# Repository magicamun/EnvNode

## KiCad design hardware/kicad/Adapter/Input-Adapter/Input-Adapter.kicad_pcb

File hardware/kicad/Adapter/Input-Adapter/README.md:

# Input Adapter — revision 0.1

Passive-DUT measurement adapter for the [Test Controller](../../MainBoards/Test-Controller/README.md).
Three CD74HC4067 multiplexers select one of **40 independent measurement inputs**:
38 ESP32 socket contacts plus MB_3V3_SYS and MB_GND. The adapter contains no ESP32.

## Connectors and power

- **J4:** DUT test plug, 2 × 19 pins, 2.54 mm pitch, 25.40 mm row spacing. From the
  top, left pins run 1–19 and right pins run 38–20. Remove the DUT ESP32 before use.
- **TP1:** two-pin header for the reference pigtail: pin 1 MB_GND, pin 2 MB_3V3_SYS.
  The cable terminates in the agreed two-pin JST-PH on a suitably revised mainboard.
  Both are measurement contacts, not adapter supply connections.
- **J1:** 2 × 5 IDC header, 2.54 mm pitch. Connect pin-for-pin to Controller J8.
  Use matching pin-1 markings and keyed cable assembly; do not assume orientation
  from connector placement on the PCB.
- J1 supplies 3V3_SYS and GND. C1–C3 provide 100 nF local decoupling for U4–U6.
  MB_GND and all DUT socket contacts remain separate from adapter supply GND.
- COM is shared by U4–U6. Enable only one multiplexer at a time. Active-low enable
  pull-ups and the ADC pulldown/filter are on the Controller, not this adapter.

## J1 cable contract

| Pin | Signal | Controller GPIO / function |
| ---: | --- | --- |
| 1 | 3V3_SYS | Adapter supply |
| 2 | GND | Supply ground |
| 3 | IN_EN1 | GPIO14; U4 enable, active low |
| 4 | IN_S3 | GPIO13 |
| 5 | IN_EN2 | GPIO26; U5 enable, active low |
| 6 | IN_S2 | GPIO27 |
| 7 | IN_EN3 | GPIO33; U6 enable, active low |
| 8 | IN_S1 | GPIO25 |
| 9 | COM / COM_IN | GPIO34 / ADC1 |
| 10 | IN_S0 | GPIO32 |

## Input routing contract

Logical inputs 1–38 retain the DUT socket numbering. Logical inputs 39 and
40 are the added reference contacts; these are not additional ESP32 socket pins.
I0–I15 denote analog multiplexer channels; S0 is the least-significant address bit.
The table records the saved PCB wiring, not a presumed sequential layout.

| Logical input | Connector.pad | Net | Multiplexer | Channel | IC pad |
| ---: | --- | --- | --- | --- | ---: |
| 1 | J4.1 | L01 | U4 | I7 | 2 |
| 2 | J4.2 | L02 | U4 | I6 | 3 |
| 3 | J4.3 | L03 | U4 | I5 | 4 |
| 4 | J4.4 | L04 | U4 | I4 | 5 |
| 5 | J4.5 | L05 | U4 | I3 | 6 |
| 6 | J4.6 | L06 | U4 | I2 | 7 |
| 7 | J4.7 | L07 | U4 | I1 | 8 |
| 8 | J4.8 | L08 | U4 | I0 | 9 |
| 9 | J4.9 | L09 | U5 | I7 | 2 |
| 10 | J4.10 | L10 | U5 | I6 | 3 |
| 11 | J4.11 | L11 | U5 | I5 | 4 |
| 12 | J4.12 | L12 | U5 | I4 | 5 |
| 13 | J4.13 | L13 | U5 | I3 | 6 |
| 14 | J4.14 | L14 | U5 | I2 | 7 |
| 15 | J4.15 | L15 | U6 | I7 | 2 |
| 16 | J4.16 | L16 | U6 | I6 | 3 |
| 17 | J4.17 | L17 | U6 | I5 | 4 |
| 18 | J4.18 | L18 | U6 | I4 | 5 |
| 19 | J4.19 | L19 | U6 | I3 | 6 |
| 20 | J4.20 | R19 | U6 | I12 | 19 |
| 21 | J4.21 | R18 | U6 | I11 | 20 |
| 22 | J4.22 | R17 | U6 | I10 | 21 |
| 23 | J4.23 | R16 | U6 | I9 | 22 |
| 24 | J4.24 | R15 | U6 | I8 | 23 |
| 25 | J4.25 | R14 | U5 | I13 | 18 |
| 26 | J4.26 | R13 | U5 | I12 | 19 |
| 27 | J4.27 | R12 | U5 | I11 | 20 |
| 28 | J4.28 | R11 | U5 | I10 | 21 |
| 29 | J4.29 | R10 | U5 | I9 | 22 |
| 30 | J4.30 | R09 | U5 | I8 | 23 |
| 31 | J4.31 | R08 | U4 | I15 | 16 |
| 32 | J4.32 | R07 | U4 | I14 | 17 |
| 33 | J4.33 | R06 | U4 | I13 | 18 |
| 34 | J4.34 | R05 | U4 | I12 | 19 |
| 35 | J4.35 | R04 | U4 | I11 | 20 |
| 36 | J4.36 | R03 | U4 | I10 | 21 |
| 37 | J4.37 | R02 | U4 | I9 | 22 |
| 38 | J4.38 | R01 | U4 | I8 | 23 |
| 39 | TP1.2 | MB_3V3_SYS | U6 | I13 | 18 |
| 40 | TP1.1 | MB_GND | U6 | I14 | 17 |

## Operation and firmware status

Continuity testing requires an unpowered DUT, its ESP32 removed, and the separate
provisioning cable disconnected. Connect the reference pigtail only to a compatible
DUT revision. Mainboard-side series protection diodes make the reference paths
unidirectional; thresholds and test current direction require physical validation.

Test firmware 0.4.0 supports 38- or 40-input profiles in its model, simulation,
comparisons and UI. The revision-0.1 fixture mapping is generated from the three
PCBs by `firmware/scripts/generate_fixture_routing.py`. Bundled legacy profiles
still use 38 inputs; new reference-aware mainboard profiles remain to be added.
The new references must not be silently treated as present on old mainboards.
Physical I/O, switching sequence and ADC settling/thresholds remain unvalidated.

The monolithic Test-Provisioning project is superseded by Input-Adapter,
Test-Controller and Module-Adapter. Earlier revisions remain in Git history.

EnvNode-owned files follow the repository LICENSE (LicenseRef-EnvNode-Use-and-Redistribution-1.0).

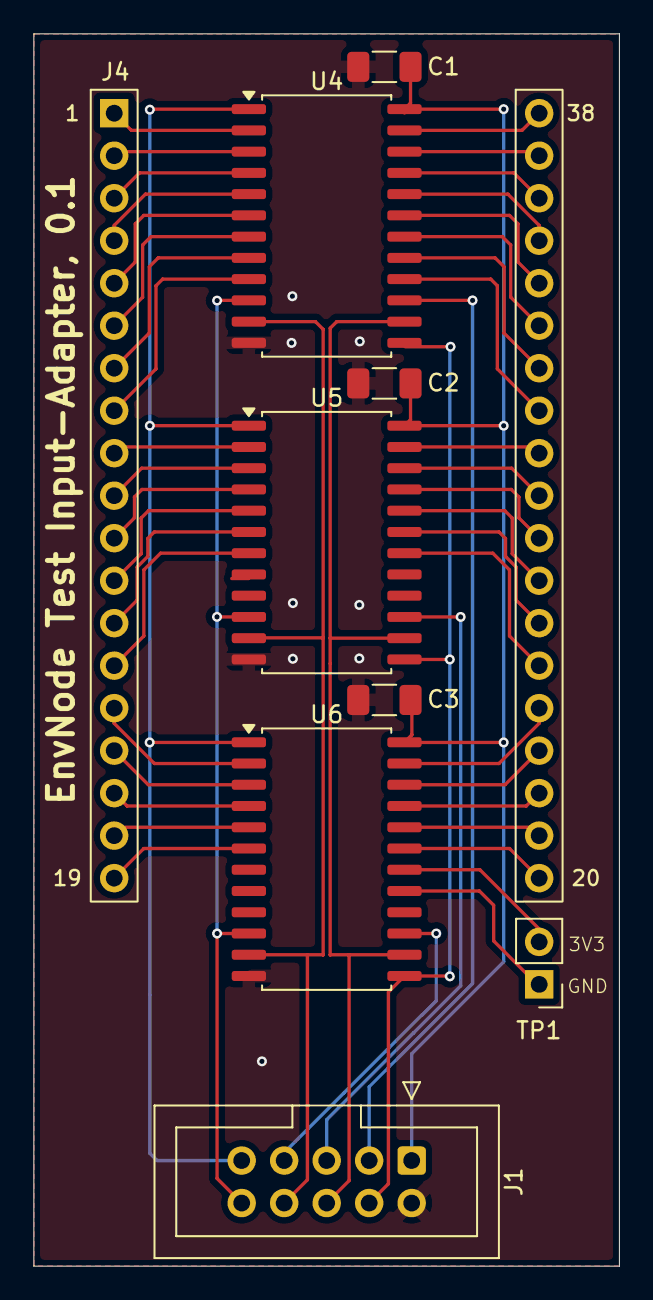
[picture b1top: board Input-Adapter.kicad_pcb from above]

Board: 2 copper layers, 35.0 x 73.7 mm, 9 parts (0 on the bottom side), 50 nets.

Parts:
C1, C2, C3: 100nF; C_1206_3216Metric_Pad1.33x1.80mm_HandSolder
J1: Conn_02x05_Odd_Even; IDC-Header_2x05_P2.54mm_Vertical
J4: ESP32_DevKitC_TestPlug; ESP32_DevKitC_TestPlug_2x19_P2.54mm_Row25.40mm
TP1: Conn_01x02_Socket; PinHeader_1x02_P2.54mm_Vertical
U4, U5, U6: CD74HC4067M; SOIC-24W_7.5x15.4mm_P1.27mm

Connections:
3V3_SYS: C1.2, C2.2, C3.2, J1.1, U4.24 (VCC), U5.24 (VCC), U6.24 (VCC)
/COM: J1.9, U4.1 (COM), U5.1 (COM), U6.1 (COM)
/IN/L01: J4.1 (L01), U4.2 (I7)
/IN/L02: J4.2 (L02), U4.3 (I6)
/IN/L03: J4.3 (L03), U4.4 (I5)
/IN/L04: J4.4 (L04), U4.5 (I4)
/IN/L05: J4.5 (L05), U4.6 (I3)
/IN/L06: J4.6 (L06), U4.7 (I2)
/IN/L07: J4.7 (L07), U4.8 (I1)
/IN/L08: J4.8 (L08), U4.9 (I0)
/IN/L09: J4.9 (L09), U5.2 (I7)
/IN/L10: J4.10 (L10), U5.3 (I6)
/IN/L11: J4.11 (L11), U5.4 (I5)
/IN/L12: J4.12 (L12), U5.5 (I4)
/IN/L13: J4.13 (L13), U5.6 (I3)
/IN/L14: J4.14 (L14), U5.7 (I2)
/IN/L15: J4.15 (L15), U6.2 (I7)
/IN/L16: J4.16 (L16), U6.3 (I6)
/IN/L17: J4.17 (L17), U6.4 (I5)
/IN/L18: J4.18 (L18), U6.5 (I4)
/IN/L19: J4.19 (L19), U6.6 (I3)
/IN/MB_3V3_SYS: TP1.2, U6.18 (I13)
/IN/MB_GND: TP1.1, U6.17 (I14)
/IN/R01: J4.38 (R01), U4.23 (I8)
/IN/R02: J4.37 (R02), U4.22 (I9)
/IN/R03: J4.36 (R03), U4.21 (I10)
/IN/R04: J4.35 (R04), U4.20 (I11)
/IN/R05: J4.34 (R05), U4.19 (I12)
/IN/R06: J4.33 (R06), U4.18 (I13)
/IN/R07: J4.32 (R07), U4.17 (I14)
/IN/R08: J4.31 (R08), U4.16 (I15)
/IN/R09: J4.30 (R09), U5.23 (I8)
/IN/R10: J4.29 (R10), U5.22 (I9)
/IN/R11: J4.28 (R11), U5.21 (I10)
/IN/R12: J4.27 (R12), U5.20 (I11)
/IN/R13: J4.26 (R13), U5.19 (I12)
/IN/R14: J4.25 (R14), U5.18 (I13)
/IN/R15: J4.24 (R15), U6.23 (I8)
/IN/R16: J4.23 (R16), U6.22 (I9)
/IN/R17: J4.22 (R17), U6.21 (I10)
/IN/R18: J4.21 (R18), U6.20 (I11)
/IN/R19: J4.20 (R19), U6.19 (I12)
/IN_EN1: J1.3, U4.15 (~E)
/IN_EN2: J1.5, U5.15 (~E)
/IN_EN3: J1.7, U6.15 (~E)
/IN_S0: J1.10, U4.10 (S0), U5.10 (S0), U6.10 (S0)
/IN_S1: J1.8, U4.11 (S1), U5.11 (S1), U6.11 (S1)
/IN_S2: J1.6, U4.14 (S2), U5.14 (S2), U6.14 (S2)
/IN_S3: J1.4, U4.13 (S3), U5.13 (S3), U6.13 (S3)
GND: C1.1, C2.1, C3.1, J1.2, U4.12 (GND), U5.12 (GND), U6.12 (GND)

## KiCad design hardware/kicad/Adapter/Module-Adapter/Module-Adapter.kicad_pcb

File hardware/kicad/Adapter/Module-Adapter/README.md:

# Module Adapter — revision 0.2

Passive test adapter between the [Test Controller](../../MainBoards/Test-Controller/README.md)
module-test output and a DUT module slot. This is not a functional module template:
there is no identification EEPROM, sensor, actuator or local power source.

- **J4:** top-side 2 × 7 IDC header, 2.54 mm pitch, connected pin-for-pin to
  Controller J3 using the matching keyed ribbon cable.
- **J1:** bottom-mounted 2 × 7 THT pin header for the DUT module socket, using
  `EnvNode-Footprints:PinHeader_2x07_P2.54mm_Vertical_Bottom`.
- **H1:** 2.7 mm mounting hole for mechanical support.
- All 14 channels connect **J4.n → J1.n** without remapping. The copper plane
  belongs only to module test contact 1 (GND); it is not an independent supply return.

## Pin contract

| Pin | DUT interface signal |
| ---: | --- |
| 1 | GND |
| 2 | +3V3_SYS |
| 3 | EEPROM_A0 (slot-dependent address strap) |
| 4 | +5V |
| 5 | I2C0_SDA |
| 6 | I2C0_SCL |
| 7 | I2C1_SDA |
| 8 | I2C1_SCL |
| 9 | AUX_GPIO1 |
| 10 | AUX_GPIO2 |
| 11 | SPI_MOSI |
| 12 | SPI_MISO |
| 13 | SPI_SCK |
| 14 | SPI_CS |

These are test contact names, not rails driven continuously by the adapter.
The selected DUT profile determines slot-specific GPIOs and whether EEPROM_A0
is tied to GND or 3V3_SYS. All contacts must remain separately selectable at the
Controller output multiplexer. Check pin-1 orientation at both ribbon connectors
and at the bottom-mounted DUT plug; use the saved pad numbering rather than
inferring numbering from a top-view image.

Continuity testing requires an unpowered DUT, removed DUT ESP32 and disconnected
provisioning cable. Move the one module adapter between slots only between tests.
See the [module-interface specification](../../../../docs/EnvNode_Module_Interface_Hardware_Specification.md).

The project footprint library path is relative to this directory:
`${KIPRJMOD}/../../Libraries/EnvNode-Footprints.pretty`. Rerun ERC/DRC after any
connector, library or routing change. Physical fit and electrical behavior still
require validation on the assembled hardware.

EnvNode-owned files follow the repository LICENSE (LicenseRef-EnvNode-Use-and-Redistribution-1.0).

Revision 0.2 rotates the IDC header for cable routing. All 14 contacts remain
pin-for-pin; use a straight IDC cable and verify pin-1 orientation. CAD reviewed;
physical acceptance of the new revision remains pending.

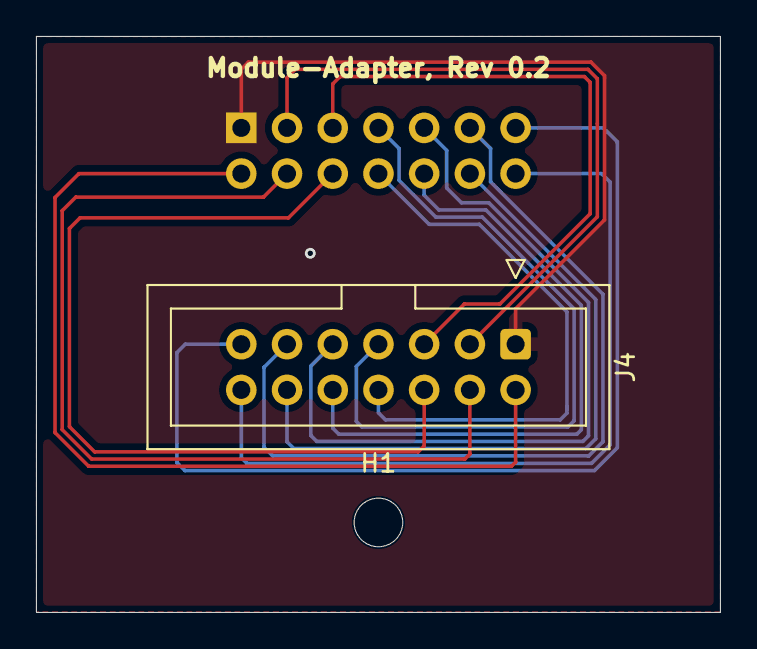
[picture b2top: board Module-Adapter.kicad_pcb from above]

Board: 2 copper layers, 38.0 x 32.0 mm, 3 parts (1 on the bottom side), 14 nets.

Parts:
H1: MountingHole; MountingHole_2.7mm_M2.5_DIN965
J1: Conn_02x07_Odd_Even; PinHeader_2x07_P2.54mm_Vertical_Bottom
J4: Conn_02x07_Odd_Even; IDC-Header_2x07_P2.54mm_Vertical

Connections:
/+3V3_SYS: J1.2, J4.2
/+5V: J1.4, J4.4
/AUX_GPIO1: J1.9, J4.9
/AUX_GPIO2: J1.10, J4.10
/EEPROM_A0: J1.3, J4.3
/GND: J1.1, J4.1
/I2C0_SCL: J1.6, J4.6
/I2C0_SDA: J1.5, J4.5
/I2C1_SCL: J1.8, J4.8
/I2C1_SDA: J1.7, J4.7
/SPI_CS: J1.14, J4.14
/SPI_MISO: J1.12, J4.12
/SPI_MOSI: J1.11, J4.11
/SPI_SCK: J1.13, J4.13

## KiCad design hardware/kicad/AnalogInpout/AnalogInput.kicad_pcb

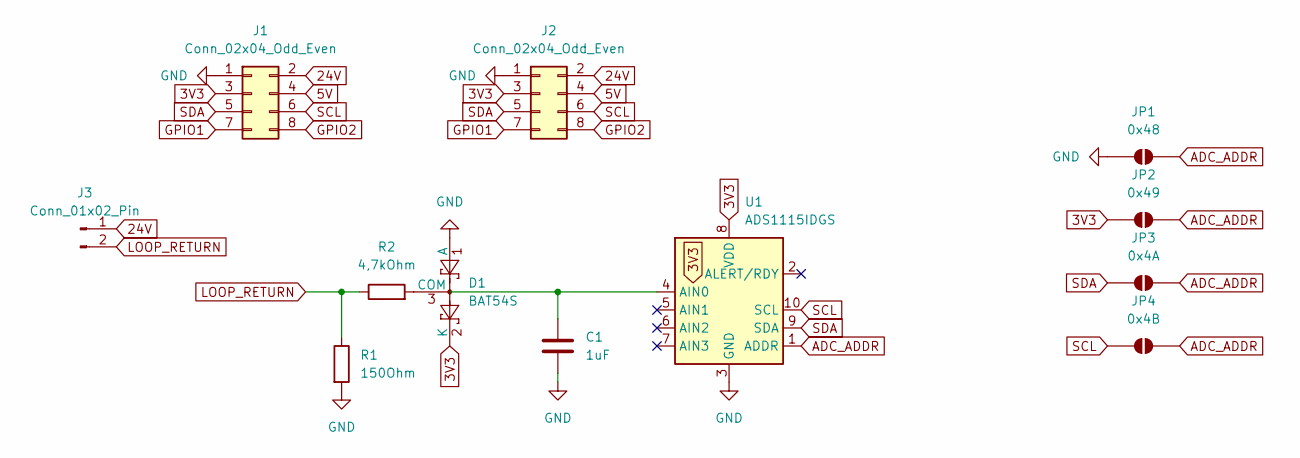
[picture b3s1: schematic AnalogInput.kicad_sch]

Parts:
C1: 1uF; C_1206_3216Metric_Pad1.33x1.80mm_HandSolder
D1: BAT54S; SOT-23
J1, J2: Conn_02x04_Odd_Even; PinSocket_2x04_P2.54mm_Vertical_Bottom
J3: Conn_01x02_Pin; PinSocket_1x02_P2.54mm_Vertical
JP1: 0x48; SolderJumper-2_P1.3mm_Open_Pad1.0x1.5mm
JP2: 0x49; SolderJumper-2_P1.3mm_Open_Pad1.0x1.5mm
JP3: 0x4A; SolderJumper-2_P1.3mm_Open_Pad1.0x1.5mm
JP4: 0x4B; SolderJumper-2_P1.3mm_Open_Pad1.0x1.5mm
R1: 150Ohm; R_1206_3216Metric_Pad1.30x1.75mm_HandSolder
R2: 4,7kOhm; R_1206_3216Metric_Pad1.30x1.75mm_HandSolder
U1: ADS1115IDGS; TSSOP-10_3x3mm_P0.5mm

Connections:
3V3: D1.2 (K), J1.3, J2.3, JP2.1 (A), U1.8 (VDD)
5V: J1.4, J2.4
24V: J1.2, J2.2, J3.1
ADC_ADDR: JP1.2 (B), JP2.2 (B), JP3.2 (B), JP4.2 (B), U1.1 (ADDR)
GND: C1.2, D1.1 (A), J1.1, J2.1, JP1.1 (A), R1.2, U1.3 (GND)
GPIO1: J1.7, J2.7
GPIO2: J1.8, J2.8
LOOP_RETURN: J3.2, R1.1, R2.1
unnamed: D1.3 (COM), R2.2
unnamed: C1.1, U1.4 (AIN0)
SCL: J1.6, J2.6, JP4.1 (A), U1.10 (SCL)
SDA: J1.5, J2.5, JP3.1 (A), U1.9 (SDA)

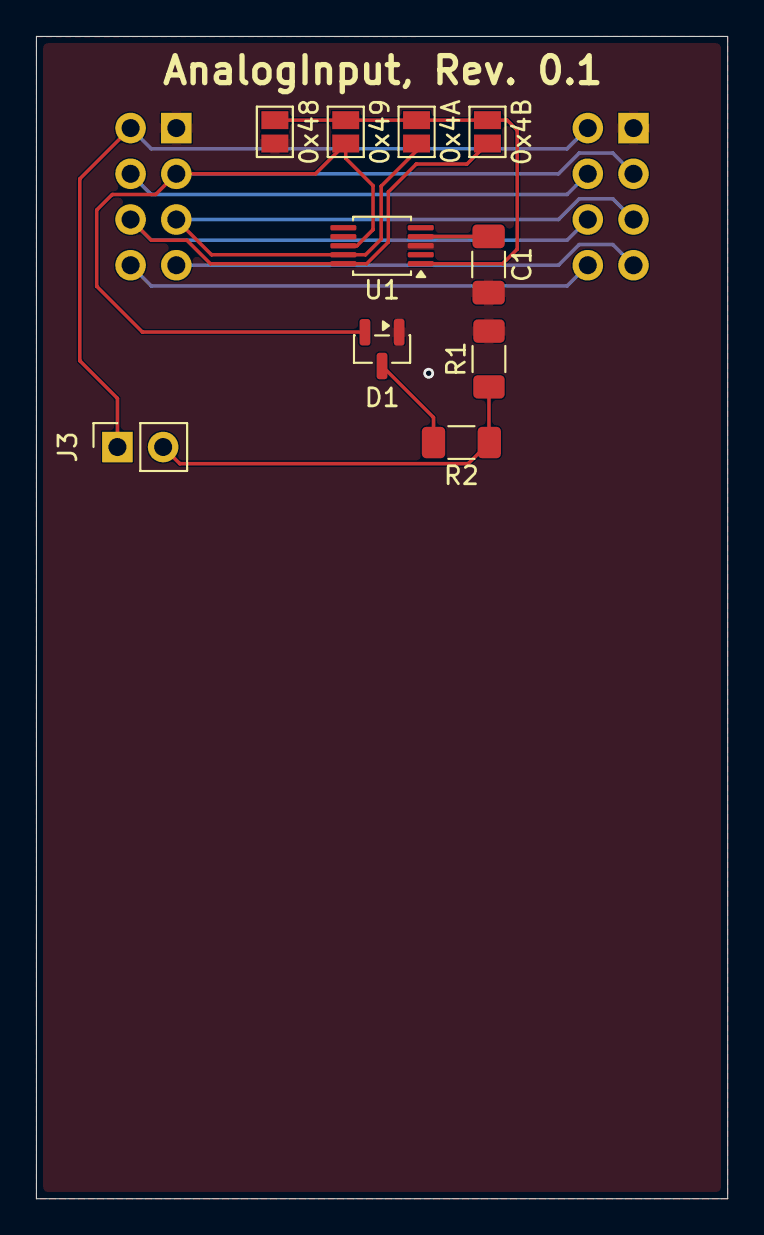
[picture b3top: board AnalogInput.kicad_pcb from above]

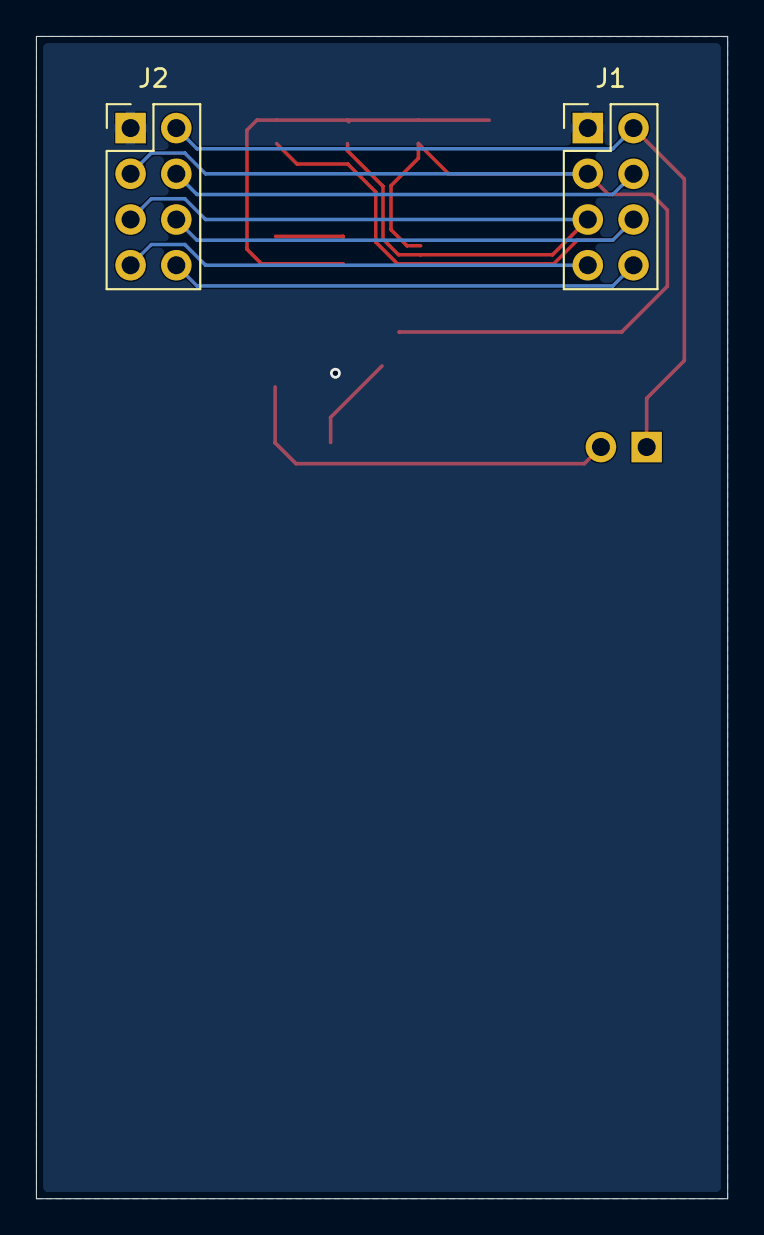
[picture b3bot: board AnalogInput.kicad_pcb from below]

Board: 2 copper layers, 38.4 x 64.6 mm, 12 parts (2 on the bottom side), 12 nets.

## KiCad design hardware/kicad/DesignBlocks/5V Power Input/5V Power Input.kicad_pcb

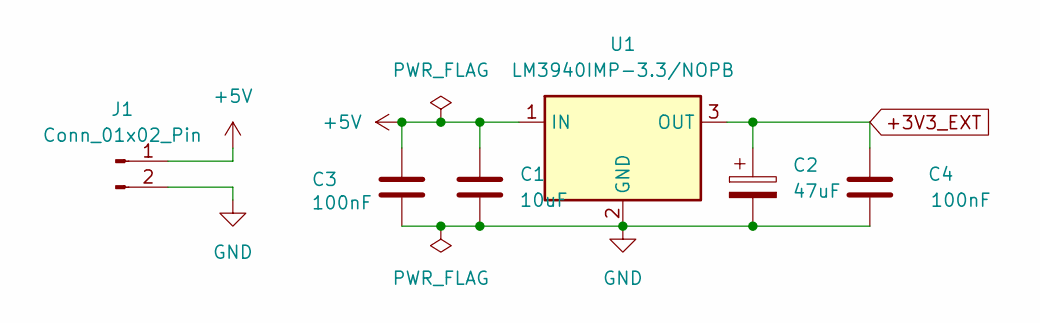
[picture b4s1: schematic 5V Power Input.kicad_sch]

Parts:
C1: 10uF; C_1206_3216Metric_Pad1.33x1.80mm_HandSolder
C2: 47uF; CP_EIA-3528-21_Kemet-B
C3, C4: 100nF; C_1206_3216Metric_Pad1.33x1.80mm_HandSolder
J1: Conn_01x02_Pin; JST_PH_B2B-PH-K_1x02_P2.00mm_Vertical
U1: LM3940IMP-3.3/NOPB; SOT-223-3_TabPin2

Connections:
+3V3_EXT: C2.1, C4.2, U1.3 (OUT)
+5V: C1.1, C3.2, J1.1, U1.1 (IN)
GND: C1.2, C2.2, C3.1, C4.1, J1.2, U1.2 (GND)

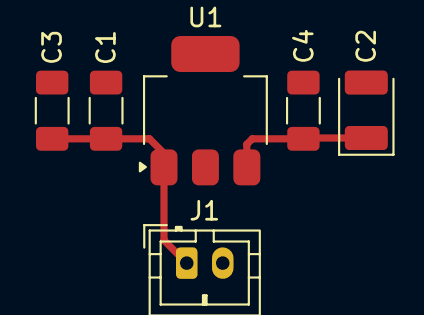
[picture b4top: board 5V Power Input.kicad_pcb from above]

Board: 2 copper layers, 6 parts (0 on the bottom side), 3 nets.
